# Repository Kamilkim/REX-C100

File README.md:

# REX-C100
Zasilacz do regulatora temperatury

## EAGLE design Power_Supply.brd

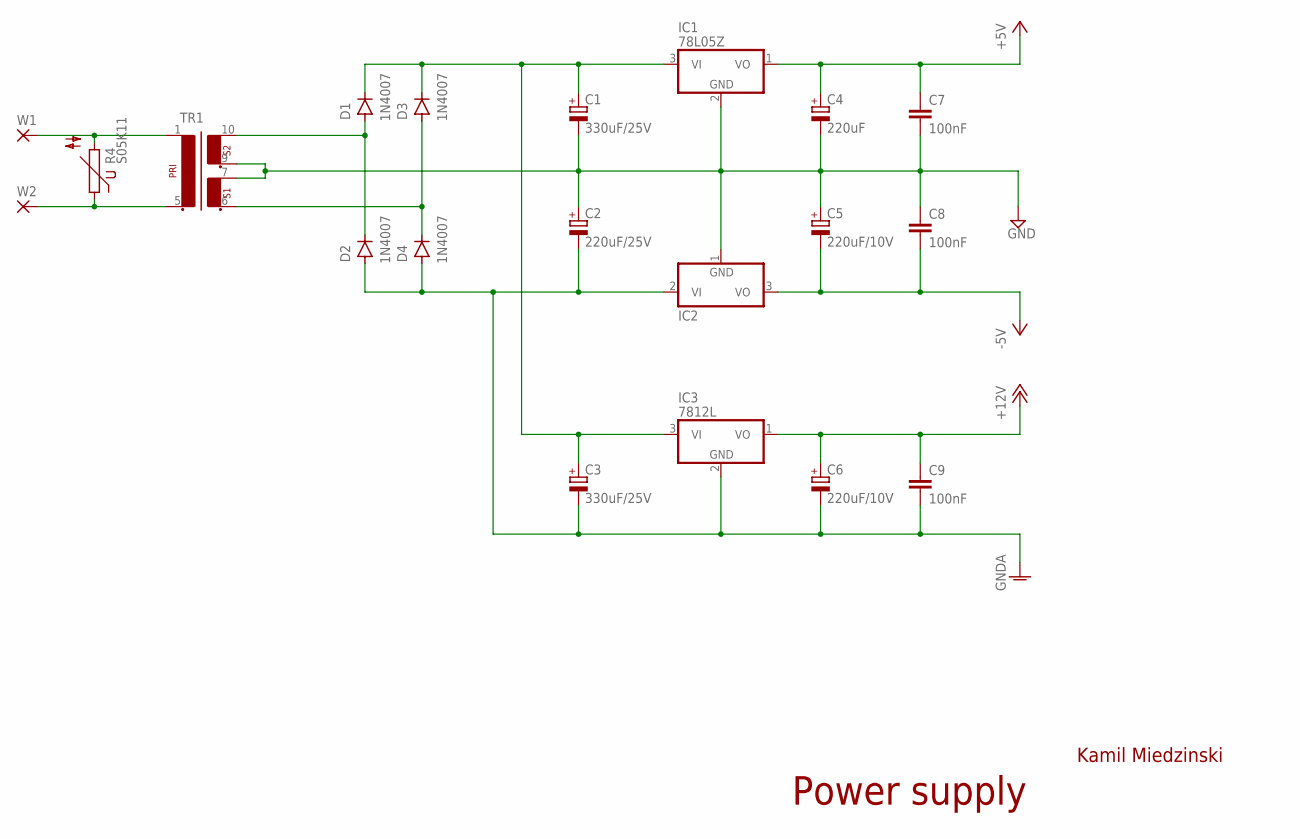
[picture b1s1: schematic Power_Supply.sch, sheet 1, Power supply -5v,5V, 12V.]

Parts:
C1, C3: 330uF/25V; E3,5-8
C2: 220uF/25V; E2,5-5
C4: 220uF; E2-4
C5, C6: 220uF/10V; E2-4
C7, C8, C9: 100nF; C025-024X044
D1, D2, D3, D4: 1N4007; DO-41
IC1: 78L05Z; TO92
IC2: 79L05Z; TO92
IC3: 7812L; TO92
R4: S05K11
TR1: TEZ_2.0VA/230V/2X9V
W1, W2: PAD_4/7; 4/7

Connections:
+5V: C4.+, C7.1, IC1.1 (VO); also elsewhere on the board
+12V: C6.+, C9.1, IC3.1 (VO); also elsewhere on the board
-5V: C5.-, C8.2, IC2.3 (VO); also elsewhere on the board
GND: C1.-, C2.+, C4.-, C5.+, C7.2, C8.1, IC1.2 (GND), IC2.1 (GND), TR1.7 (4), TR1.9 (5); also elsewhere on the board
GNDA: C2.-, C3.-, C6.-, C9.2, D2.A, D4.A, IC2.2 (VI), IC3.2 (GND); also elsewhere on the board
unnamed: R4.2, TR1.1, W1.1
unnamed: R4.1, TR1.5 (2), W2.1
unnamed: C1.+, C3.+, D1.C, D3.C, IC1.3 (VI), IC3.3 (VI)
unnamed: D1.A, D2.C, TR1.10 (6)
unnamed: D3.A, D4.C, TR1.6 (3)

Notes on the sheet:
Power supply
Kamil Miedzinski

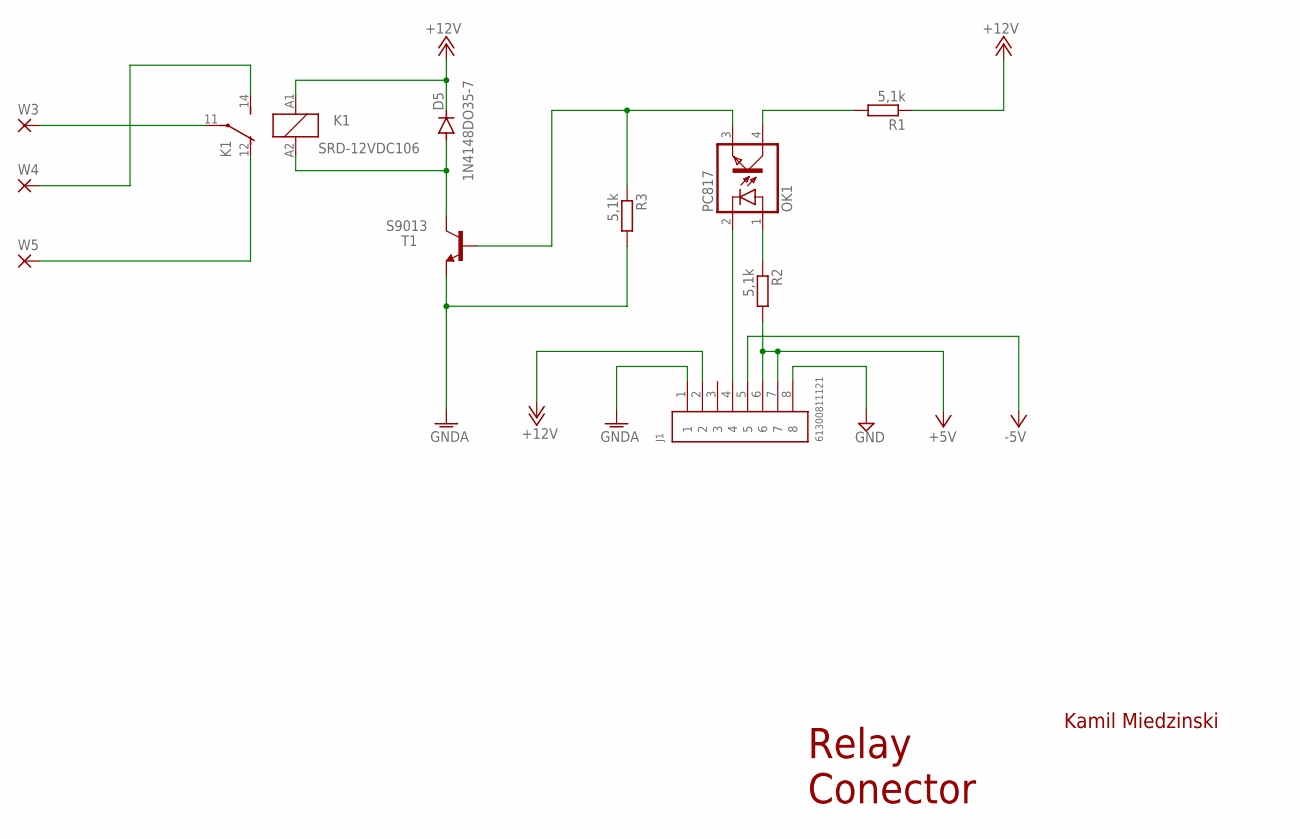
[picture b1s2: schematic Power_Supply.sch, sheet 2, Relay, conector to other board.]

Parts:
D5: 1N4148DO35-7; DO35-7
J1: 61300811121
K1: SRD-12VDC106; ZN5
OK1: PC817; DIL04
R1, R2, R3: 5,1k; 0204/7
T1: S9013; TO92
W3, W4, W5: PAD_4/7; 4/7

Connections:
+5V: J1.6, J1.7, R2.2; also elsewhere on the board
+12V: D5.C, J1.2, K1.A1 (1), R1.1; also elsewhere on the board
-5V: J1.5; also elsewhere on the board
GND: J1.8; also elsewhere on the board
GNDA: J1.1, R3.2, T1.1 (E); also elsewhere on the board
unnamed: K1.11, W3.1
unnamed: K1.12 (O), W5.1
unnamed: K1.14 (S), W4.1
unnamed: OK1.1 (A), R2.1
unnamed: J1.4, OK1.2 (C)
unnamed: OK1.3 (EMIT), R3.1, T1.2 (B)
unnamed: D5.A, K1.A2 (2), T1.3 (C)
unnamed: OK1.4 (COL), R1.2

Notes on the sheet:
Relay Conector
Kamil Miedzinski

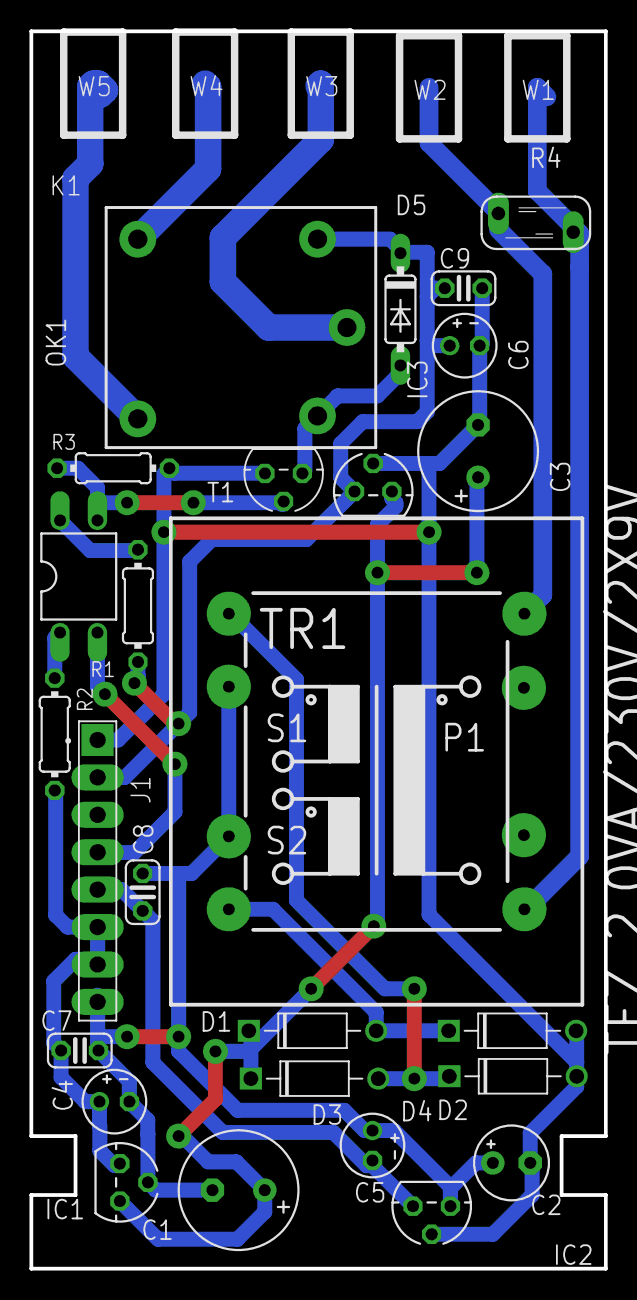
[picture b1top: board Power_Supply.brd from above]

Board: 2 copper layers, 39.0 x 84.0 mm, 31 parts (0 on the bottom side), 18 nets.

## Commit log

2019-11-08 Render
2019-11-08 Rendered image
2019-11-08 esdt
2019-11-10 test
2019-11-10 circle
2019-11-10 none circle
